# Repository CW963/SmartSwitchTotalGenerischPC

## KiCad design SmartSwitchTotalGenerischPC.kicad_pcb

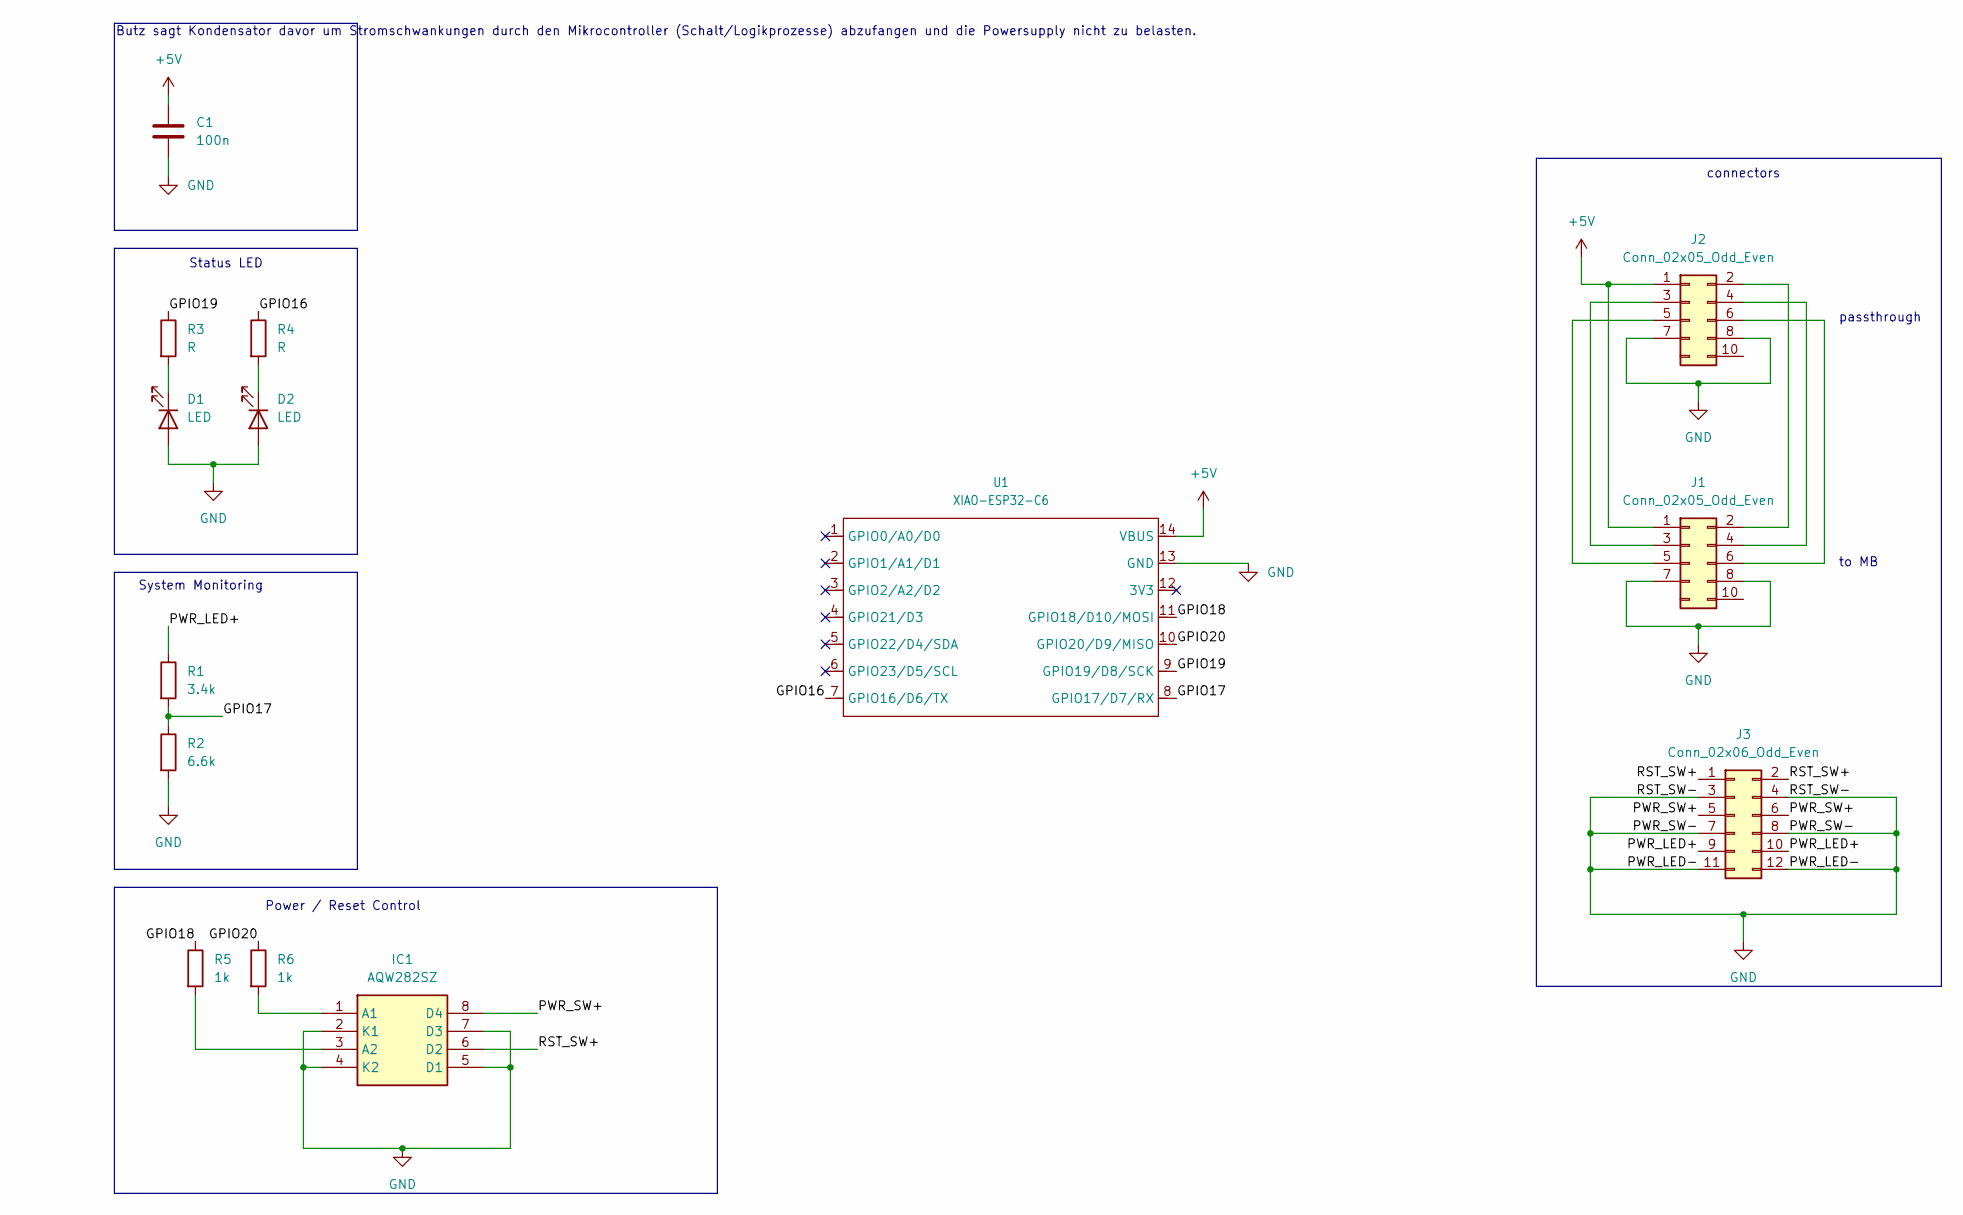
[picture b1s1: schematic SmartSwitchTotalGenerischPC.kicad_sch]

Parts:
C1: 100n; C_0805_2012Metric_Pad1.18x1.45mm_HandSolder
D1, D2: LED; LED_0805_2012Metric_Pad1.15x1.40mm_HandSolder
IC1: AQW282SZ; SOP254P680X230-8N; Mouser Part Number 769-AQW282SZ
J1: Conn_02x05_Odd_Even; PinSocket_2x05_P2.54mm_Horizontal
J2: Conn_02x05_Odd_Even; PinHeader_2x05_P2.54mm_Vertical_SMD
J3: Conn_02x06_Odd_Even; PinHeader_2x06_P2.54mm_Horizontal
R1: 3.4k; R_0805_2012Metric_Pad1.20x1.40mm_HandSolder
R2: 6.6k; R_0805_2012Metric_Pad1.20x1.40mm_HandSolder
R3, R4: R; R_0805_2012Metric_Pad1.20x1.40mm_HandSolder
R5, R6: 1k; R_0805_2012Metric_Pad1.20x1.40mm_HandSolder
U1: XIAO-ESP32-C6; XIAO-ESP32C6-DIP

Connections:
+5V: C1.1, J1.1 (USB0_5V), J2.1 (USB0_5V), U1.14 (VBUS)
/GPIO16: R4.1, U1.7 (GPIO16/D6/TX)
/GPIO17: R1.2, R2.1, U1.8 (GPIO17/D7/RX)
/GPIO18: R5.1, U1.11 (GPIO18/D10/MOSI)
/GPIO19: R3.1, U1.9 (GPIO19/D8/SCK)
/GPIO20: R6.1, U1.10 (GPIO20/D9/MISO)
/PWR_LED+: J3.9, J3.10, R1.1
/PWR_SW+: IC1.8 (D4), J3.5, J3.6
/RST_SW+: IC1.6 (D2), J3.1, J3.2
GND: C1.2, D1.2 (A), D2.2 (A), IC1.2 (K1), IC1.4 (K2), IC1.5 (D1), IC1.7 (D3), J1.7 (USB0_GND), J1.8 (USB1_GND), J2.7 (USB0_GND), J2.8 (USB1_GND), J3.3, J3.4, J3.7, J3.8, J3.11, J3.12, R2.2, U1.13 (GND)
unnamed: D1.1 (K), R3.2
unnamed: D2.1 (K), R4.2
unnamed: IC1.1 (A1), R6.2
unnamed: IC1.3 (A2), R5.2
unnamed: J1.5 (USB0_D+), J2.5 (USB0_D+)
unnamed: J1.3 (USB0_D-), J2.3 (USB0_D-)
unnamed: J1.2 (USB1_5V), J2.2 (USB1_5V)
unnamed: J1.6 (USB1_D+), J2.6 (USB1_D+)
unnamed: J1.4 (USB1_D-), J2.4 (USB1_D-)

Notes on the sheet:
Status LED
Power / Reset Control
passthrough
connectors
Butz sagt Kondensator davor um Stromschwankungen durch den Mikrocontroller (Schalt/Logikprozesse) abzufangen und die Powersupply nicht zu belasten.
to MB
System Monitoring

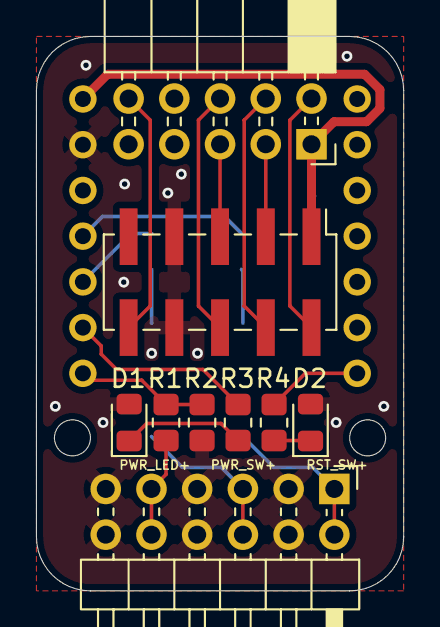
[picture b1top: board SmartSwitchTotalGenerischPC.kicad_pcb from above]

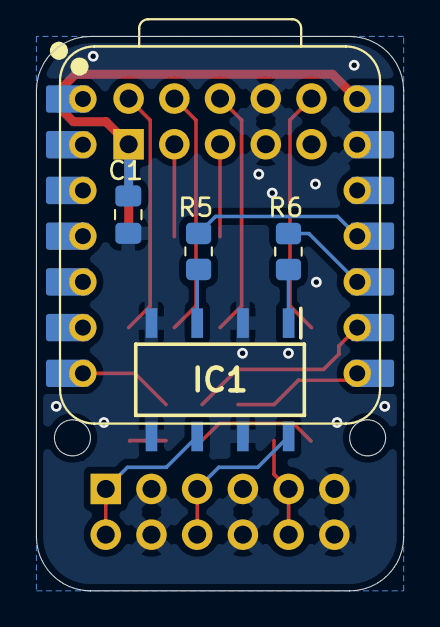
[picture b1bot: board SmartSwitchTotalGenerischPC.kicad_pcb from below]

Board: 2 copper layers, 20.4 x 30.8 mm, 14 parts (5 on the bottom side), 19 nets.

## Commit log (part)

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2025-05-17 first prototype revision
